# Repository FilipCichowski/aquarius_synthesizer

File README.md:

Hi, 
This synth was designed as beginner project. Sound is created by four NE555 and, after mixing, filtered by MFOS WSG TL071-based filter.

The PWM generator is unnecessary complex. You can redesign this project and use single 555.
Rocker switch holes are on a joint. You can make them a bit bigger. 

You can create PCB at home as single-layer PCB with jumpers, but I included gerber files which you can send to PCB factory. I reccomend second option.

Released under CC-BY license. Filip Cichowski © 2020.

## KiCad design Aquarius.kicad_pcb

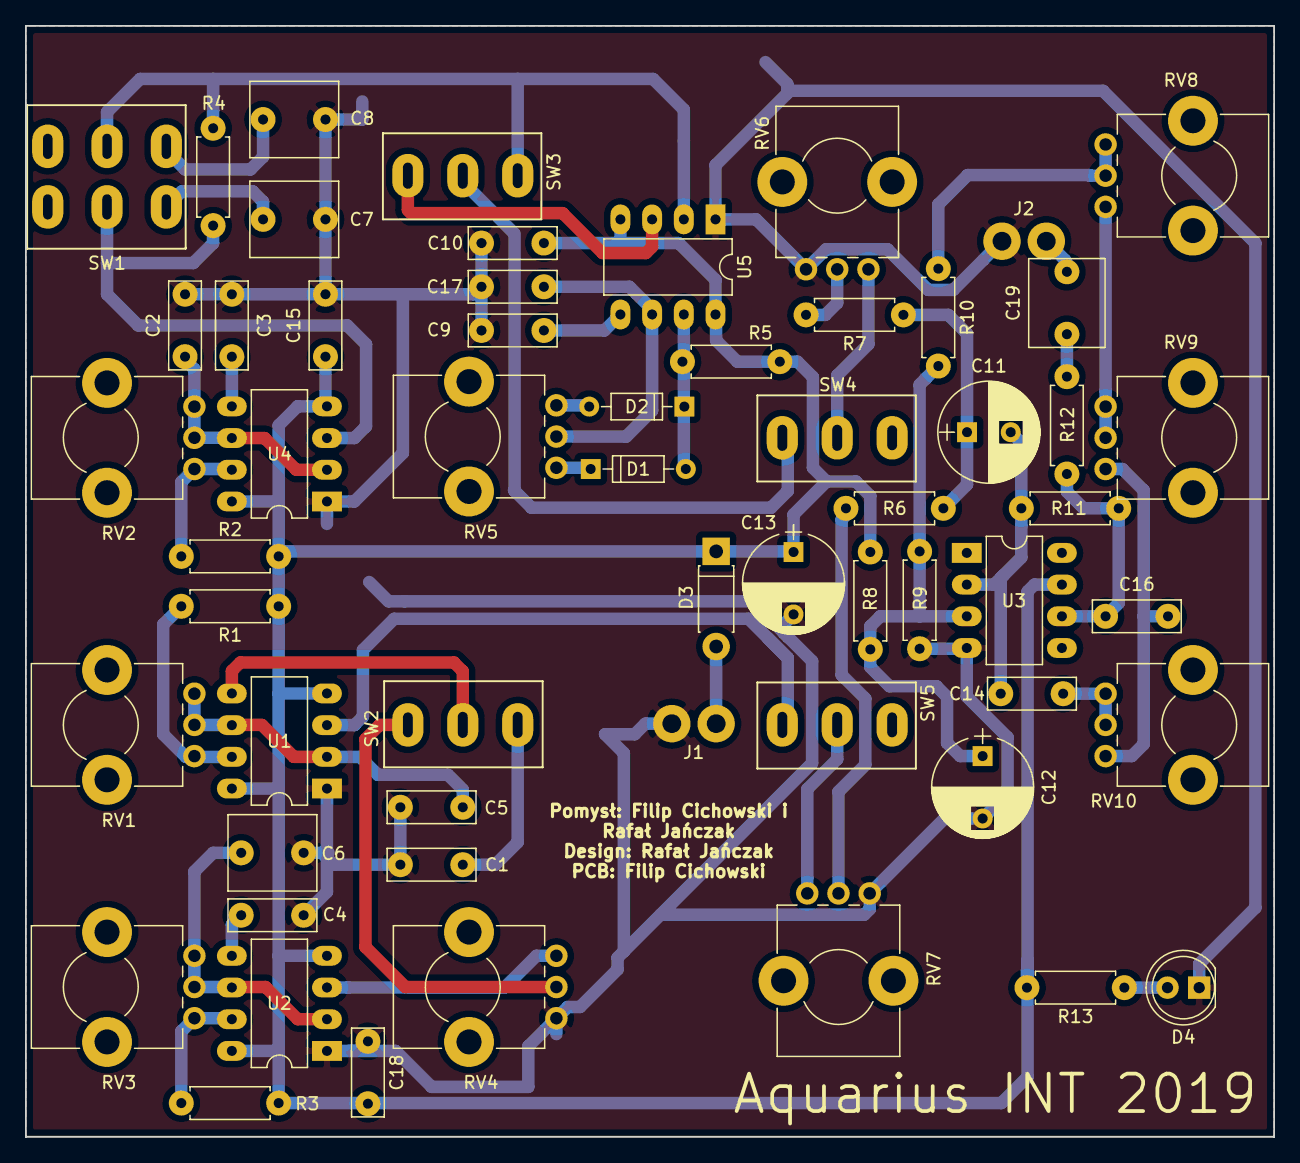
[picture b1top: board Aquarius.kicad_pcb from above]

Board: 2 copper layers, 100.0 x 89.0 mm, 58 parts (0 on the bottom side), 42 nets.

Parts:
C1, C3, C4, C9: 10nF; Monolit-maly
C2, C5, C10: 22nF; Monolit-maly
C6, C7, C8, C19: 1uF; Monolit-duzy
C11: 10uF; CP_Radial_D8.0mm_P3.50mm
C12, C13: 100uF; CP_Radial_D8.0mm_P5.00mm
C14, C16: 470pF; Monolit-maly
C15, C17, C18: 100nF; Monolit-maly
D1, D2: 1N4148; D_DO-35_SOD27_P7.62mm_Horizontal
D3: 1N5819; D_DO-41_SOD81_P7.62mm_Horizontal
D4: LED; LED_D5.0mm
J1: ZAS; WireConnection_1.50mmDrill
J2: AUDIO; WireConnection_1.50mmDrill
R1, R2, R3, R4, R5: 10K; Rezystor7,8
R6, R7: 120K; Rezystor7,8
R8, R9: 100K; Rezystor7,8
R10, R12, R13: 1K; Rezystor7,8
R11: 10M; Rezystor7,8
RV1, RV2, RV3, RV8: 1M; Potentiometer_Bourns_PTV09A-1_Horizontal
RV4, RV5, RV6, RV7, RV9: 100K; Potentiometer_Bourns_PTV09A-1_Horizontal
RV10: 220K; Potentiometer_Bourns_PTV09A-1_Horizontal
SW1: SW_DPDT_x2; DPDT
SW2, SW3: SW_SPDT; SPDT
SW4, SW5: SW_SPST; SPDT
U1, U2, U4, U5: NE555; DIP-8_W7.62mm_LongPads
U3: TL071; DIP-8_W7.62mm_LongPads

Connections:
+12V: C13.1, C15.1, C17.1, C18.1, D3.1, R1.2, R2.2, R3.2, R5.2, R8.1, R13.2, U1.4, U1.8, U2.4, U2.8, U3.7, U4.4, U4.8, U5.4, U5.8
GND: C1.2, C2.2, C3.2, C4.2, C5.1, C6.1, C7.1, C8.1, C9.1, C10.1, C12.2, C13.2, C15.2, C17.2, C18.2, D4.1, J1.1, J2.2, R9.2, RV4.3, RV6.3, RV7.3, U1.1, U2.1, U3.4, U4.1, U5.1
LFO: RV4.2, SW2.3
MIX1: R7.2, RV6.2
MIX2: R6.2, RV7.2
unnamed: C1.1, SW2.1
unnamed: C2.1, RV2.1, RV2.2, U4.2, U4.6
unnamed: C3.1, U4.5
unnamed: C4.1, U2.5
unnamed: C5.2, RV1.1, RV1.2, U1.2, U1.6
unnamed: C6.2, RV3.1, RV3.2, U2.2, U2.6
unnamed: C7.2, SW1.4
unnamed: C8.2, SW1.1
unnamed: C9.2, U5.5
unnamed: C10.2, RV5.2, U5.6
unnamed: C11.1, R6.1, R7.1
unnamed: C11.2, C14.1, R11.1, U3.2
unnamed: C12.1, R8.2, R9.1, R10.2, U3.3
unnamed: C14.2, RV10.2, RV10.3
unnamed: C16.1, R11.2, R12.2, U3.6
unnamed: C16.2, RV9.1, RV10.1
unnamed: C19.1, R12.1
unnamed: C19.2, J2.1
unnamed: D1.1, RV5.3
unnamed: D1.2, D2.1, R5.1, U5.7
unnamed: D2.2, RV5.1
unnamed: D3.2, J1.2
unnamed: D4.2, R13.1
unnamed: R1.1, RV1.3, U1.7
unnamed: R2.1, RV2.3, U4.7
unnamed: R3.1, RV3.3, U2.7
unnamed: R4.2, SW1.5, U4.3
unnamed: RV4.1, U2.3
unnamed: RV6.1, SW4.2
unnamed: RV7.1, SW5.2
unnamed: RV8.1, RV9.2, RV9.3
unnamed: SW2.2, U1.5
unnamed: SW3.1, U5.3
RESO: R10.1, RV8.2, RV8.3
VCO1: R4.1, SW1.2, SW3.3, U5.2
VCO1OUT: SW3.2, SW4.1
VCO2OUT: SW5.1, U1.3
